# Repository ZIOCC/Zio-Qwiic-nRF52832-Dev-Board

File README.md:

# Zio Qwiic nRF52832 Dev Board

> This product can be available for purchase [here](https://www.smart-prototyping.com/Zio-nRF52832-Dev-Board-Qwiic-NRF-BLE).

> If you're looking for the nRF52832 Bluetooth module, you can check it out [here](https://www.smart-prototyping.com/nrf52832-Bluetooth-NFC-Module)

#### Description

This nRF52832 Dev Board is based on a well designed nRF52832 BLE module (E73). We’ve flashed Adafruit’s nrf52 Arduino bootloader for you, which makes it compatible with Arduino IDE. The dev board is open source hardware, for any makers and engineers they can embed the nRF52832 module into their project once the prototype is verified. 

The board breakouts all the pins from the module, and the pins for the NRF antenna. There is one NFC antenna with the package, which can be easily soldered to the through holes. 

We also added two Qwiic connectors, so you can use our Qwiic modules to instantly start I2C projects.

For the main IC nRF52832, you can check it from Nordic official website [here](https://www.nordicsemi.com/Products/Low-power-short-range-wireless/nRF52832). 

> Note: the Pins are not pre-soldered.

#### Specification

* BLE MCU: nrf52832
* USB UART MCU: SILICON LABS CP2104
* Weight: 8.1g
* Dimension: 30.0 x 55.3mm

#### Links

* [nrf52832 Datasheet](http://infocenter.nordicsemi.com/pdf/nRF52832_PS_v1.4.pdf)
* [nrf52832 official link](https://www.nordicsemi.com/eng/Products/Bluetooth-low-energy/nRF52832)
* [nrf52832 module Schematic](https://www.smart-prototyping.com/image/data/2_components/Bluetooth/101920%20nrf52832%20Bluetooth%20Module%20(CE,%20FCC,%20Half-Cut%20Hole)/nrf52832_module_schematic.png)
* [Eagle file and source file for Dev board](https://github.com/ZIOCC/Zio-Qwiic-nRF52832-Dev-Board)
* [Schematic for Dev Board](https://github.com/ZIOCC/Zio-Qwiic-nRF52832-Dev-Board/blob/master/Zio%20Qwiic%20nRF52832%20Dev%20Board%20Schematic%20PDF.pdf)
* [Adafruit nRF52 Arduino Bootloader](https://github.com/adafruit/Adafruit_nRF52_Arduino_Bootloader)

> ###### About Zio
> Zio is a new line of open sourced, compact, and grid layout boards, fully integrated for Arduino and Qwiic ecosystem. Designed ideally for wearables, robotics, small-space limitations or other on the go projects. Check out other awesome Zio products [here](https://www.smart-prototyping.com/Zio).

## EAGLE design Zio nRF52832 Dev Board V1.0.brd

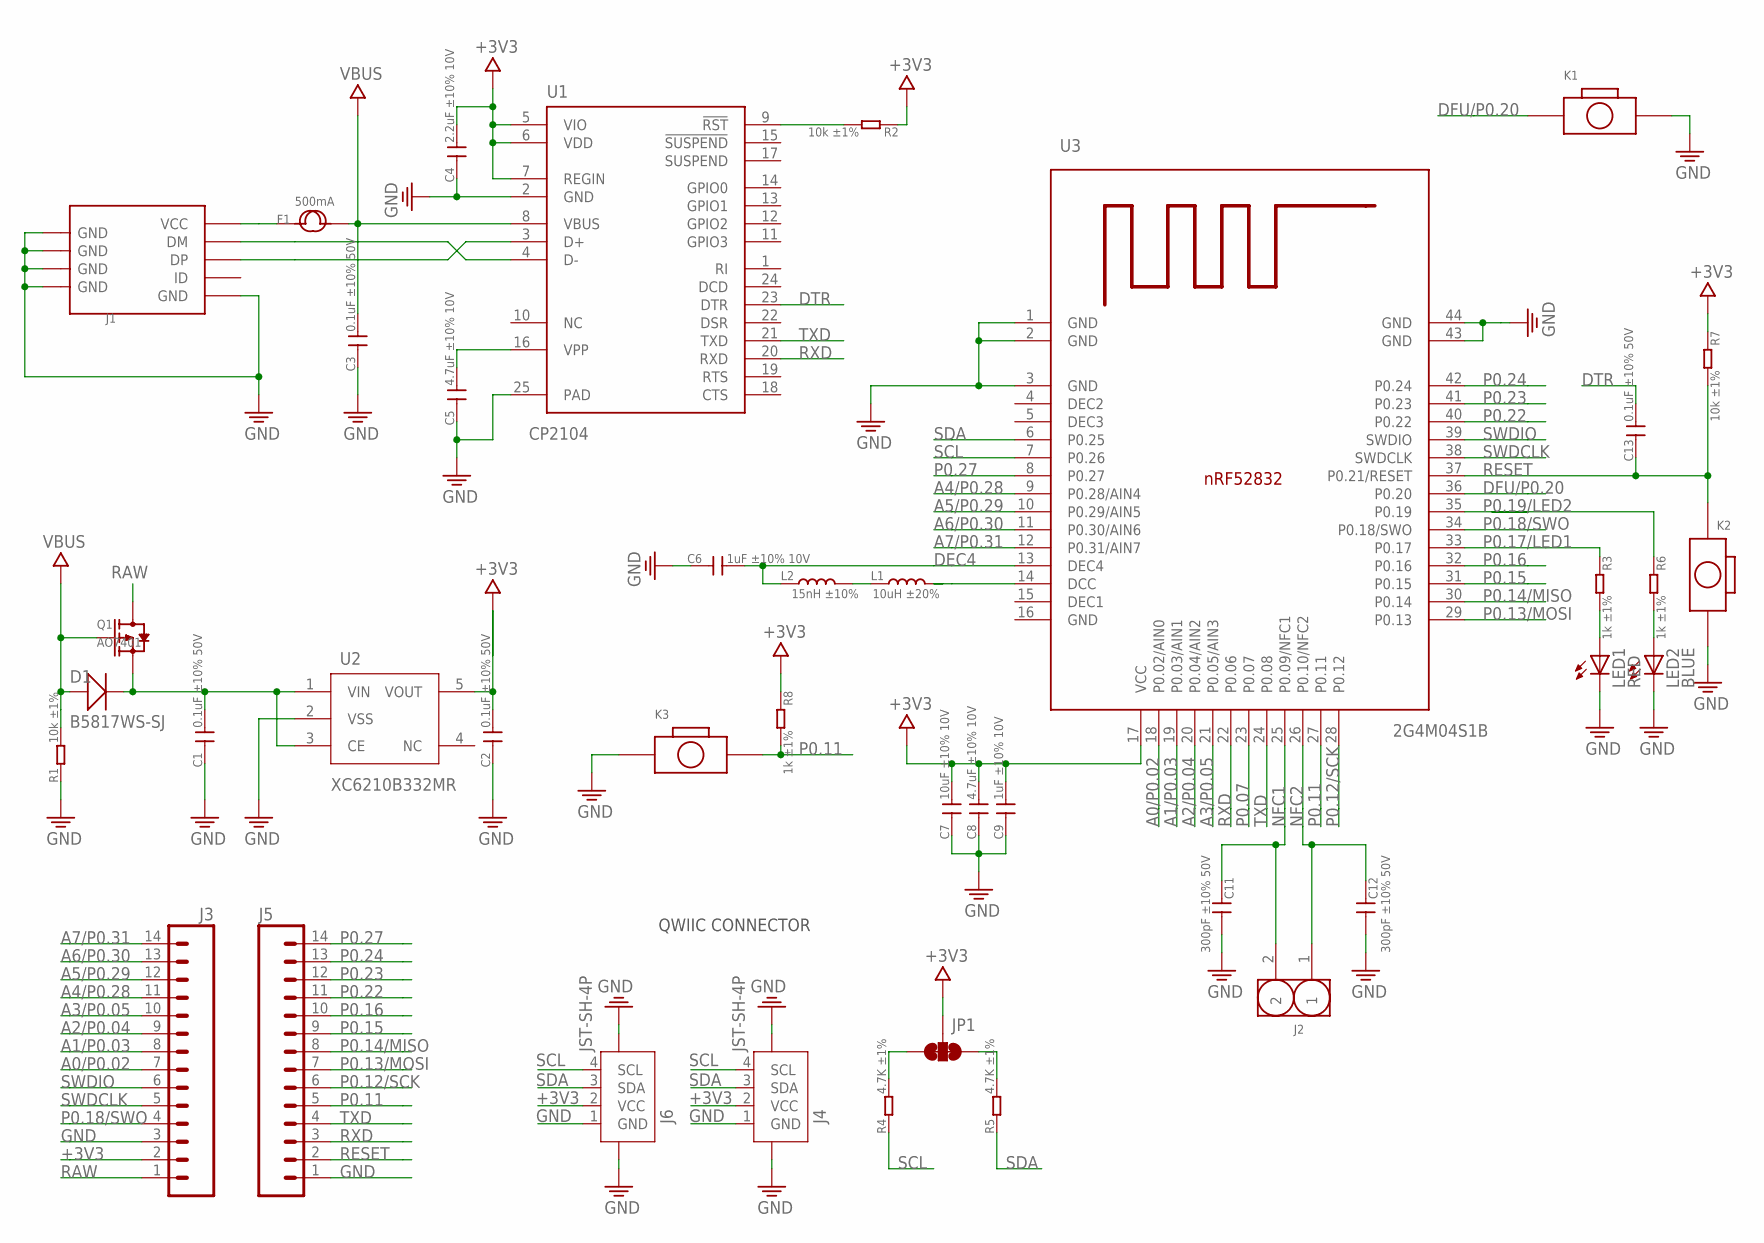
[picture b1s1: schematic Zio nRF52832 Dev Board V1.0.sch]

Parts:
C1, C2, C3, C13: 0.1uF ±10% 50V; C0603
C4: 2.2uF ±10% 10V; C0603
C5, C8: 4.7uF ±10% 10V; C0603
C6, C9: 1uF ±10% 10V; C0603
C7: 10uF ±10% 10V; C0603
C11, C12: 300pF ±10% 50V; C0603
D1: B5817WS-SJ; SOD323
F1: 500mA; 1206
J1: USB-MICROE; MICRO-SMD
J2: HEADER-2P-65/35MIL; 2P-2.54-65/35MIL
J3, J5: HEADER-14P; 14P-SCREW-2.54
J4, J6: JST-SH-4P; JST-SH-4P-90
JP1: SMT-JUMPER_3_2-NC_TRACE
K1, K2, K3: BOTTON-2PSKRKAEE020; SKRKAEE020
L1: 10uH ±20%; L0603
L2: 15nH ±10%; L0402
LED1: RED; CHIPLED_0603
LED2: BLUE; CHIPLED_0603
Q1: AO7401; SOT-323
R1, R2, R7: 10k ±1%; R0603
R3, R6, R8: 1k ±1%; R0603
R4, R5: 4.7K ±1%; R0603
U1: CP2104; QFN24_4X4
U2: XC6210B332MR; SOT23-5
U3: 2G4M04S1B; 2G4M04S1B_NRF52832

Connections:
+3V3: C2.2, C4.2, C7.2, C8.2, C9.2, J3.2, J4.2 (VCC), J6.2 (VCC), JP1.2, R2.1, R7.1, R8.1, U1.5 (VIO), U1.6 (VDD), U1.7 (REGIN), U2.5 (VOUT), U3.17 (VCC)
A0/P0.02: J3.7, U3.18 (P0.02/AIN0)
A1/P0.03: J3.8, U3.19 (P0.03/AIN1)
A2/P0.04: J3.9, U3.20 (P0.04/AIN2)
A3/P0.05: J3.10, U3.21 (P0.05/AIN3)
A4/P0.28: J3.11, U3.9 (P0.28/AIN4)
A5/P0.29: J3.12, U3.10 (P0.29/AIN5)
A6/P0.30: J3.13, U3.11 (P0.30/AIN6)
A7/P0.31: J3.14, U3.12 (P0.31/AIN7)
DEC4: C6.2, L2.1, U3.13 (DEC4)
DFU/P0.20: K1.1, U3.36 (P0.20)
DTR: C13.2, U1.23 (DTR)
GND: C1.1, C2.1, C3.1, C4.1, C5.1, C6.1, C7.1, C8.1, C9.1, C11.2, C12.2, J1.P5 (GND), J1.S1 (GND), J1.S2 (GND), J1.S3 (GND), J1.S4 (GND), J3.3, J4.1 (GND), J4.5, J4.6, J5.1, J6.1 (GND), J6.5, J6.6, K1.2, K2.2, K3.1, LED1.C, LED2.C, R1.1, U1.2 (GND), U1.25 (PAD), U2.2 (VSS), U3.1 (GND), U3.2 (GND), U3.3 (GND), U3.43 (GND), U3.44 (GND)
unnamed: L1.1, L2.2
unnamed: J1.P3 (DP), U1.3 (D+)
unnamed: R2.2, U1.9 (!RST!)
unnamed: J1.P2 (DM), U1.4 (D-)
unnamed: F1.1, J1.P1 (VCC)
unnamed: LED2.A, R6.2
unnamed: C5.2, U1.16 (VPP)
unnamed: LED1.A, R3.2
unnamed: L1.2, U3.14 (DCC)
unnamed: JP1.3, R4.2
unnamed: JP1.1, R5.2
NFC1: C11.1, J2.2, U3.25 (P0.09/NFC1)
NFC2: C12.1, J2.1, U3.26 (P0.10/NFC2)
P0.07: U3.23 (P0.07)
P0.11: J5.5, K3.2, R8.2, U3.27 (P0.11)
P0.12/SCK: J5.6, U3.28 (P0.12)
P0.13/MOSI: J5.7, U3.29 (P0.13)
P0.14/MISO: J5.8, U3.30 (P0.14)
P0.15: J5.9, U3.31 (P0.15)
P0.16: J5.10, U3.32 (P0.16)
P0.17/LED1: R3.1, U3.33 (P0.17)
P0.18/SWO: J3.4, U3.34 (P0.18/SWO)
P0.19/LED2: R6.1, U3.35 (P0.19)
P0.22: J5.11, U3.40 (P0.22)
P0.23: J5.12, U3.41 (P0.23)
P0.24: J5.13, U3.42 (P0.24)
P0.27: J5.14, U3.8 (P0.27)
RAW: J3.1, Q1.3 (D)
RESET: C13.1, J5.2, K2.1, R7.2, U3.37 (P0.21/RESET)
RXD: J5.3, U1.20 (RXD), U3.22 (P0.06)
SCL: J4.4 (SCL), J6.4 (SCL), R4.1, U3.7 (P0.26)
SDA: J4.3 (SDA), J6.3 (SDA), R5.1, U3.6 (P0.25)
SWDCLK: J3.5, U3.38 (SWDCLK)
SWDIO: J3.6, U3.39 (SWDIO)
TXD: J5.4, U1.21 (TXD), U3.24 (P0.08)
VBUS: C3.2, D1.+, F1.2, Q1.1 (G), R1.2, U1.8 (VBUS)
VIN: C1.2, D1.-, Q1.2 (S), U2.1 (VIN), U2.3 (CE)

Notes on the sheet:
QWIIC CONNECTOR

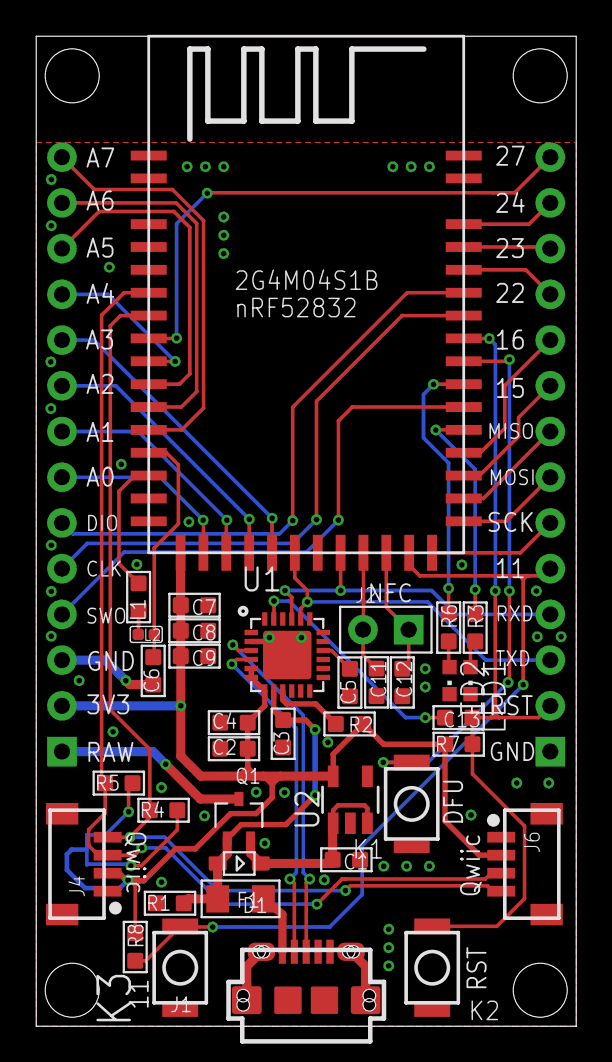
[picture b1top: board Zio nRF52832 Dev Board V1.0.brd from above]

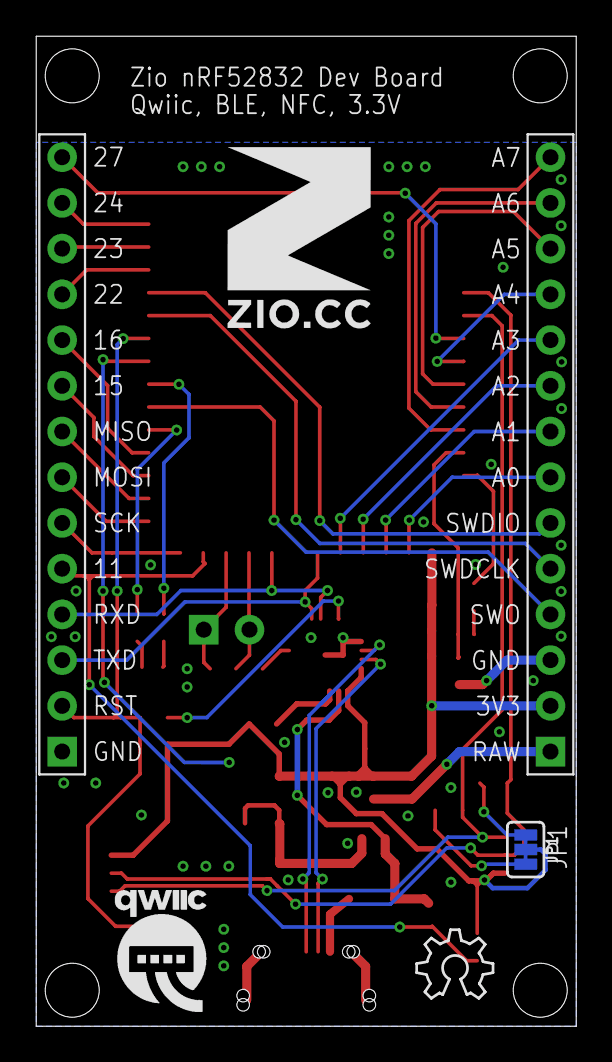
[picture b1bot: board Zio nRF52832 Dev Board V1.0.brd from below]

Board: 2 copper layers, 30.0 x 55.0 mm, 43 parts (6 on the bottom side), 49 nets.

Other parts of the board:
U$8: 10MM
U$11: QWIIC-LOGO-MEDIUM
U$12: OSHW_6X150_NOTEXT
